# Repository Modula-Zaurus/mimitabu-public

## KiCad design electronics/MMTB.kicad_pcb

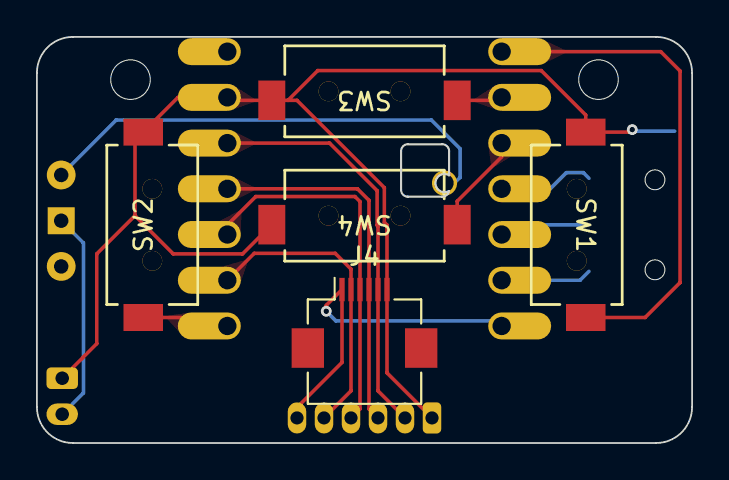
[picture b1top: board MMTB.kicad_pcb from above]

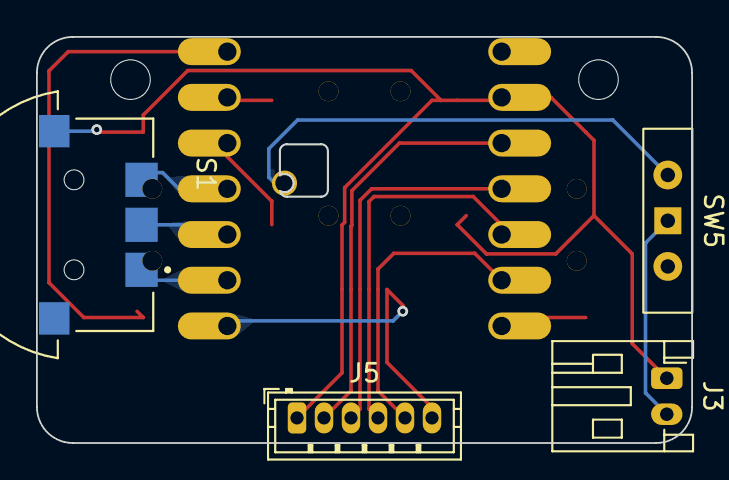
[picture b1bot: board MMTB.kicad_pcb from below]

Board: 2 copper layers, 36.4 x 22.6 mm, 12 parts (5 on the bottom side), 15 nets.

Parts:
H1, H2: MountingHole; m2_Screw_Hole
J3: Conn_01x02_Socket; JST_PH_S2B-PH-K_1x02_P2.00mm_Horizontal
J4: Conn_01x06_Socket; Hirose_FH12-6S-0.5SH_1x06-1MP_P0.50mm_Horizontal
J5: Conn_01x06_Socket; JST_ZH_B6B-ZR_1x06_P1.50mm_Vertical
S1: TMHU27; SW_TMHU27
SW1, SW2, SW3, SW4: SW_PUSH; SW_D2LS-11_2_OMR
SW5: SW_Wuerth_450301014042; SW_Slide-03_Wuerth-WS-SLTV_10x2.5x6.4_P2.54mm
U1: xiao-ble; xiao-ble-smd-simplified

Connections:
+3.3V: J4.5, J5.2, U1.12 (3V3)
BAT: SW5.2 (C), U1.19 (BAT)
EXT_1: S1.2, U1.4 (A11/0.29)
EXT_2: S1.T, U1.5 (A8_SDA/0.04_H)
EXT_3: S1.1, U1.6 (A9_SCL/0.05_H)
GND: J3.1, J4.6, J5.1, S1.G_1, SW1.1, SW2.2, SW3.2, SW4.2, U1.13 (GND)
IO 0: SW1.2, U1.1 (A2/0.02_H)
IO 1: SW2.1, U1.8 (B9_RX/1.12)
IO 2: SW3.1, U1.2 (A4/0.03_H)
IO 3: SW4.1, U1.3 (A10/0.28)
MOTION2: J4.3, J5.4, U1.10 (A5_MISO/1.14)
SCLK2: J4.2, J5.5, U1.9 (A7_SCK/1.13)
SDIO2: J4.4, J5.3, U1.11 (A6_MOSI/1.15)
VBAT: J3.2, SW5.1 (B)
nCS2: J4.1, J5.6, U1.7 (B8_TX/1.11)
